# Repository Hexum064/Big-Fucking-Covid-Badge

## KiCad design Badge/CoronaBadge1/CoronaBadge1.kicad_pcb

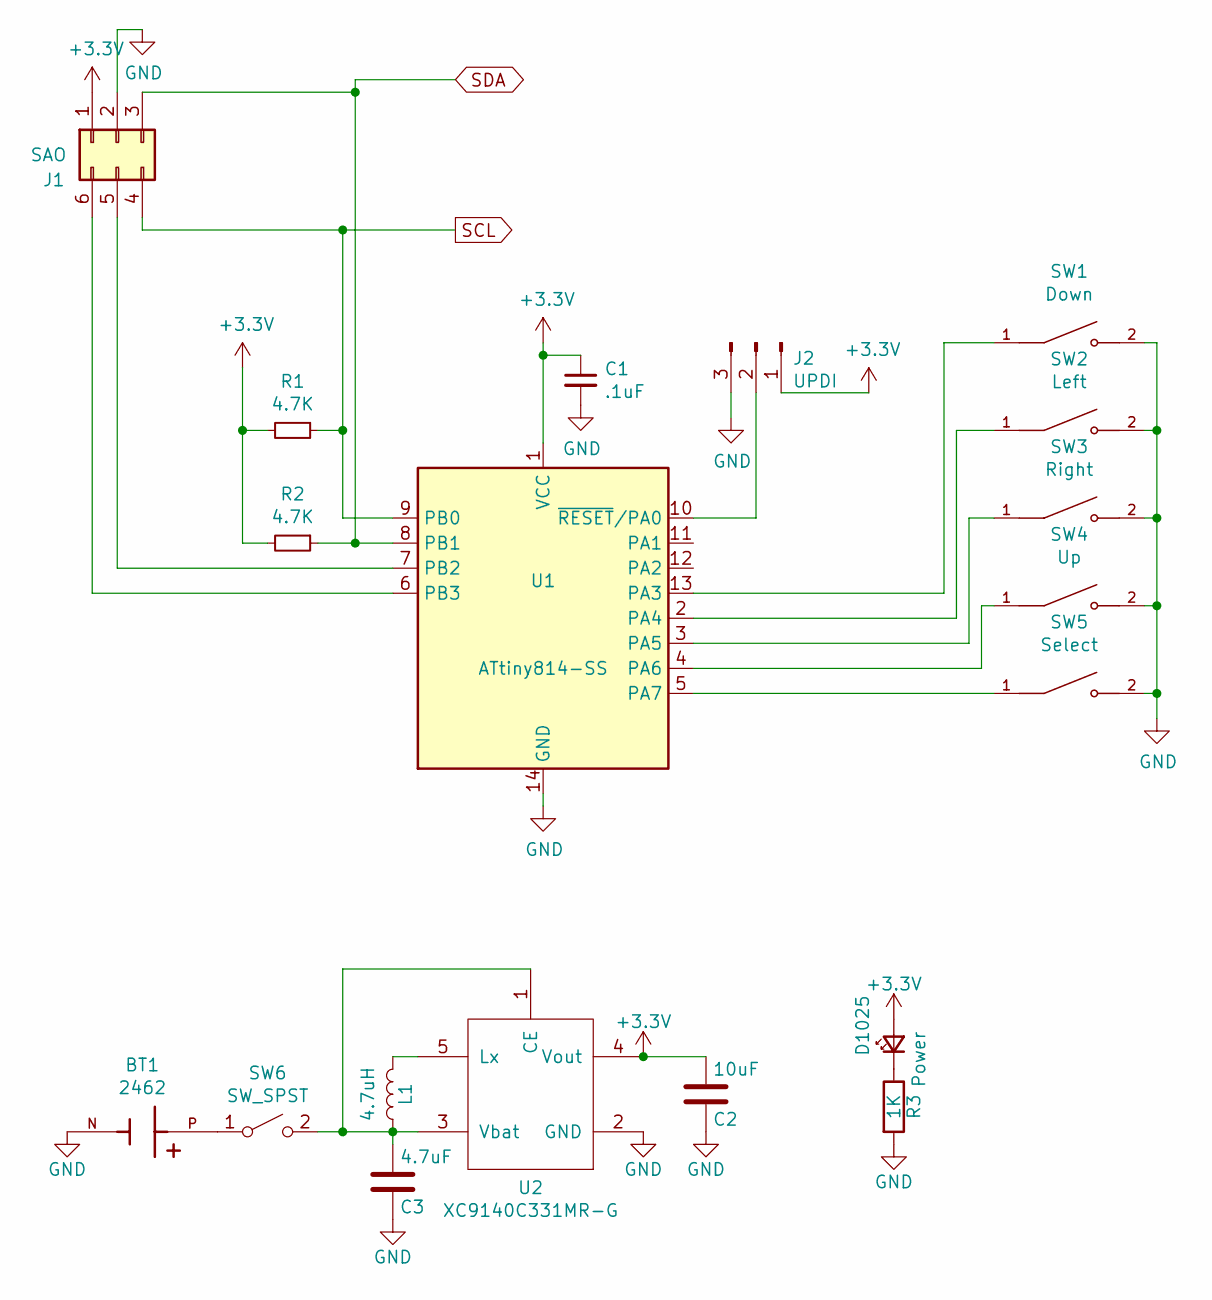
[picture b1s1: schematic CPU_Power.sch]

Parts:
BT1: 2462; BAT_2462; PARTREV G
C1: .1uF; C_0603
C2: 10uF; C_0603
C3: 4.7uF; C_0603
D1025: Power; LED_0603
J1: SAO; Pin_Header_Straight_2x03_Pitch2.54mm
J2: UPDI; Pin_Header_Straight_1x03_Pitch2.54mm
L1: 4.7uH; Inductor_Taiyo-Yuden_MD-3030
R1, R2: 4.7K; R_0603
R3: 1K; R_0603
SW1: Down; SW_PTS636_SM43J_SMTR_LFS
SW2: Left; SW_PTS636_SM43J_SMTR_LFS
SW3: Right; SW_PTS636_SM43J_SMTR_LFS
SW4: Up; SW_PTS636_SM43J_SMTR_LFS
SW5: Select; SW_PTS636_SM43J_SMTR_LFS
SW6: SW_SPST; MSS3VTR
U1: ATtiny814-SS; SOIC-14_3.9x8.7mm_P1.27mm
U2: XC9140C331MR-G; SOT-23-5

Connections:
+3V3: C1.1, C2.2, D1025.2 (A), J1.1, J2.1, R1.2, R2.2, U1.1 (VCC), U2.4 (Vout); also elsewhere on the board
GND: BT1.N, C1.2, C2.1, C3.1, J1.2, J2.3, R3.2, SW1.2, SW2.2, SW3.2, SW4.2, SW5.2, U1.14 (GND), U2.2 (GND); also elsewhere on the board
unnamed: BT1.P, SW6.1 (A)
unnamed: C3.2, L1.1, SW6.2 (B), U2.1 (CE), U2.3 (Vbat)
unnamed: D1025.1 (K), R3.1
unnamed: J1.5, U1.7 (PB2)
unnamed: J1.6, U1.6 (PB3)
unnamed: J2.2, U1.10 (~RESET~/PA0)
unnamed: L1.2, U2.5 (Lx)
unnamed: SW1.1, U1.13 (PA3)
unnamed: SW2.1, U1.2 (PA4)
unnamed: SW3.1, U1.3 (PA5)
unnamed: SW4.1, U1.4 (PA6)
unnamed: SW5.1, U1.5 (PA7)
SCL: J1.4, R1.1, U1.9 (PB0); also elsewhere on the board
SDA: J1.3, R2.1, U1.8 (PB1); also elsewhere on the board

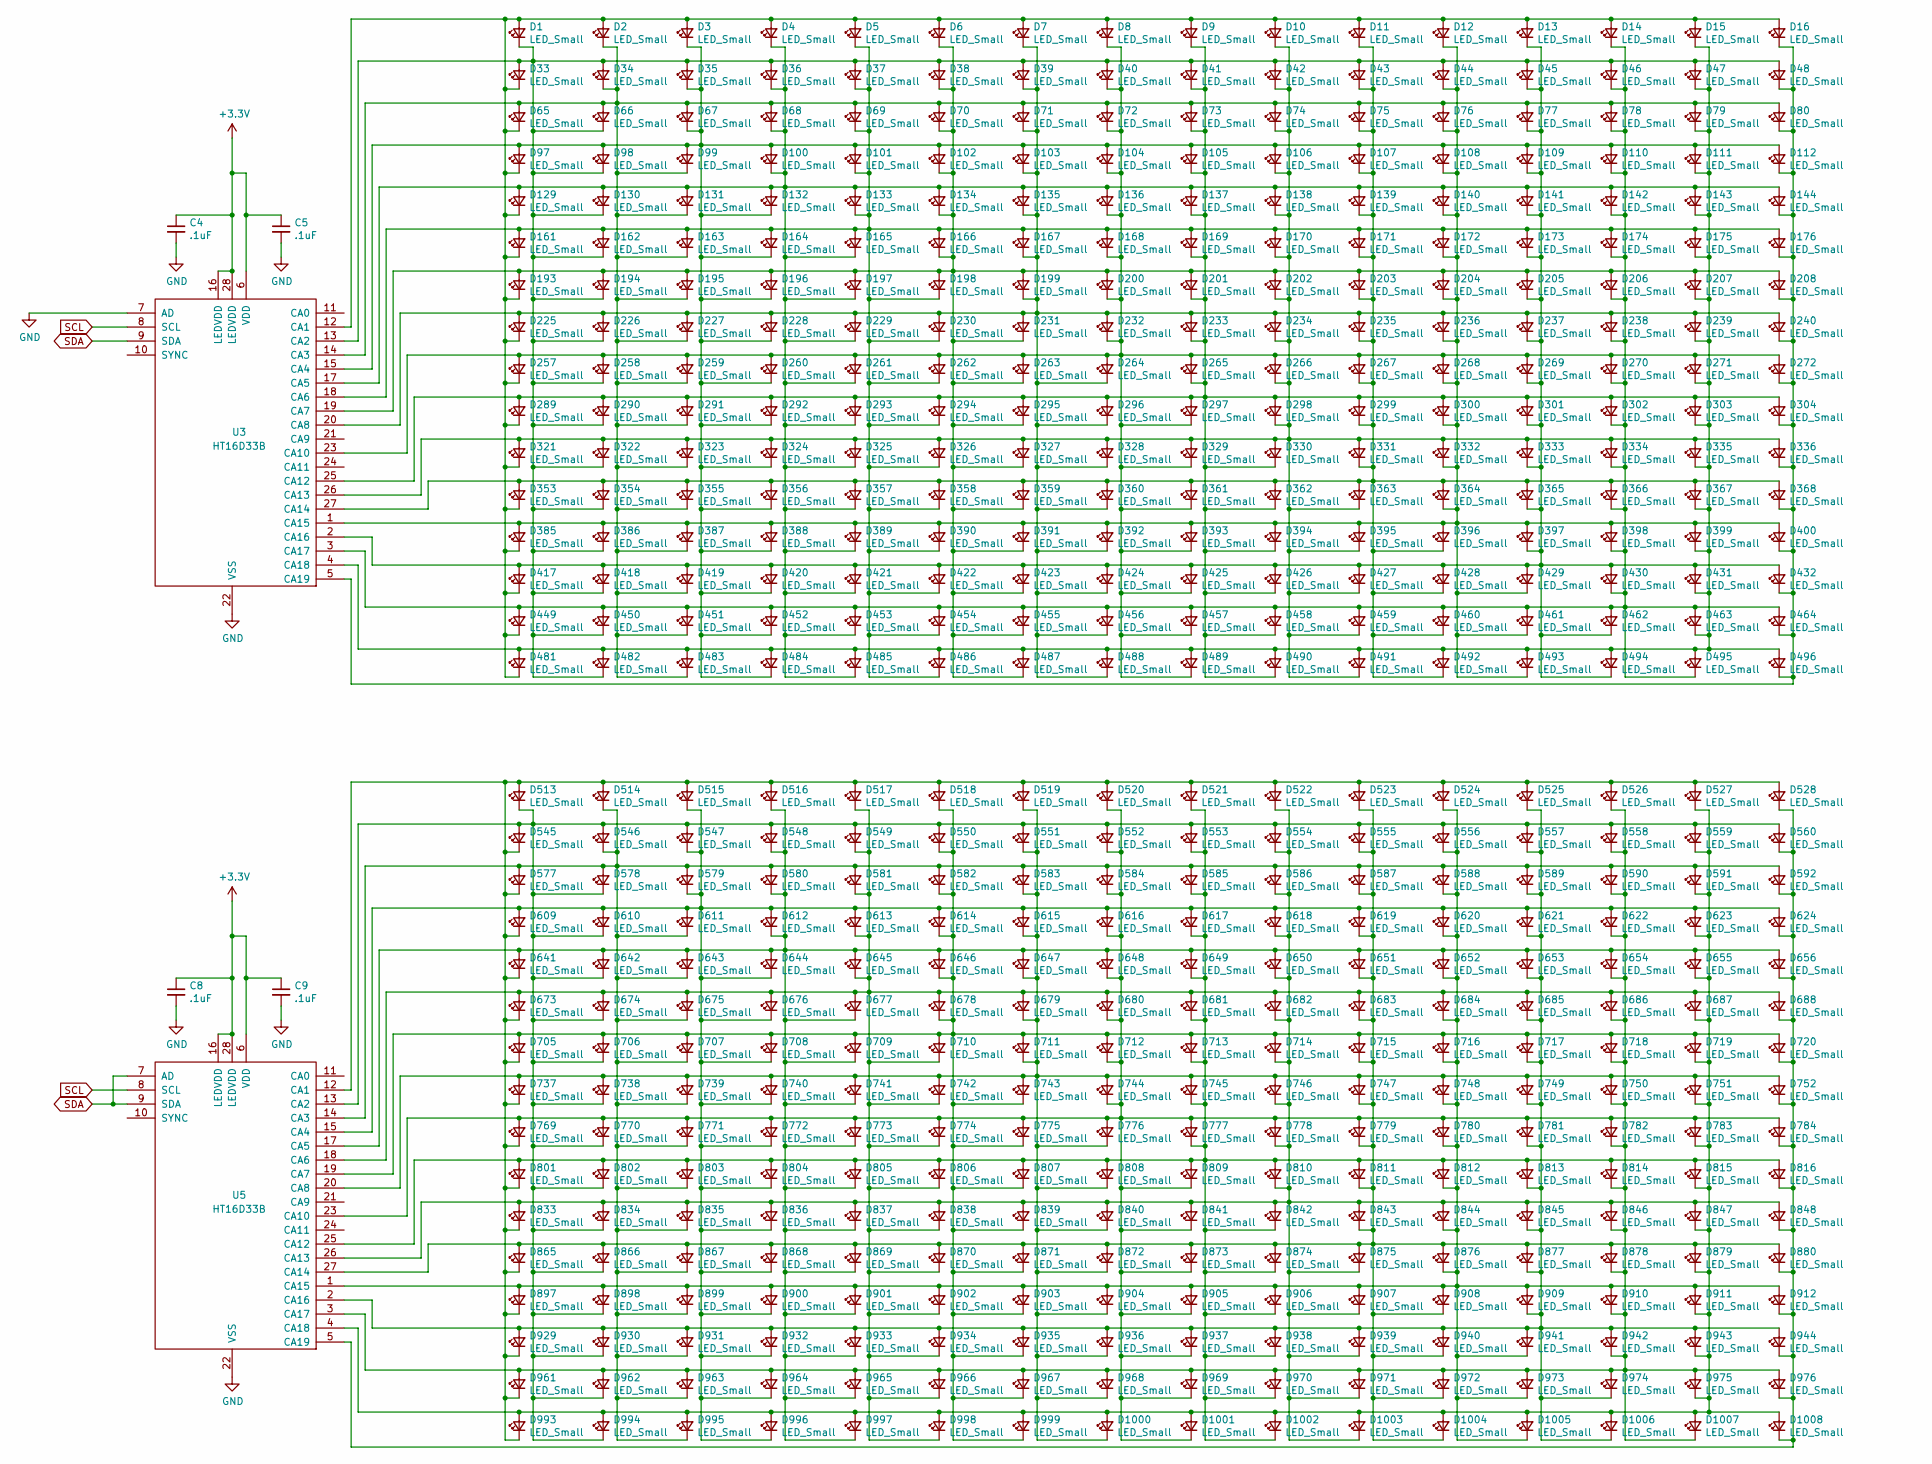
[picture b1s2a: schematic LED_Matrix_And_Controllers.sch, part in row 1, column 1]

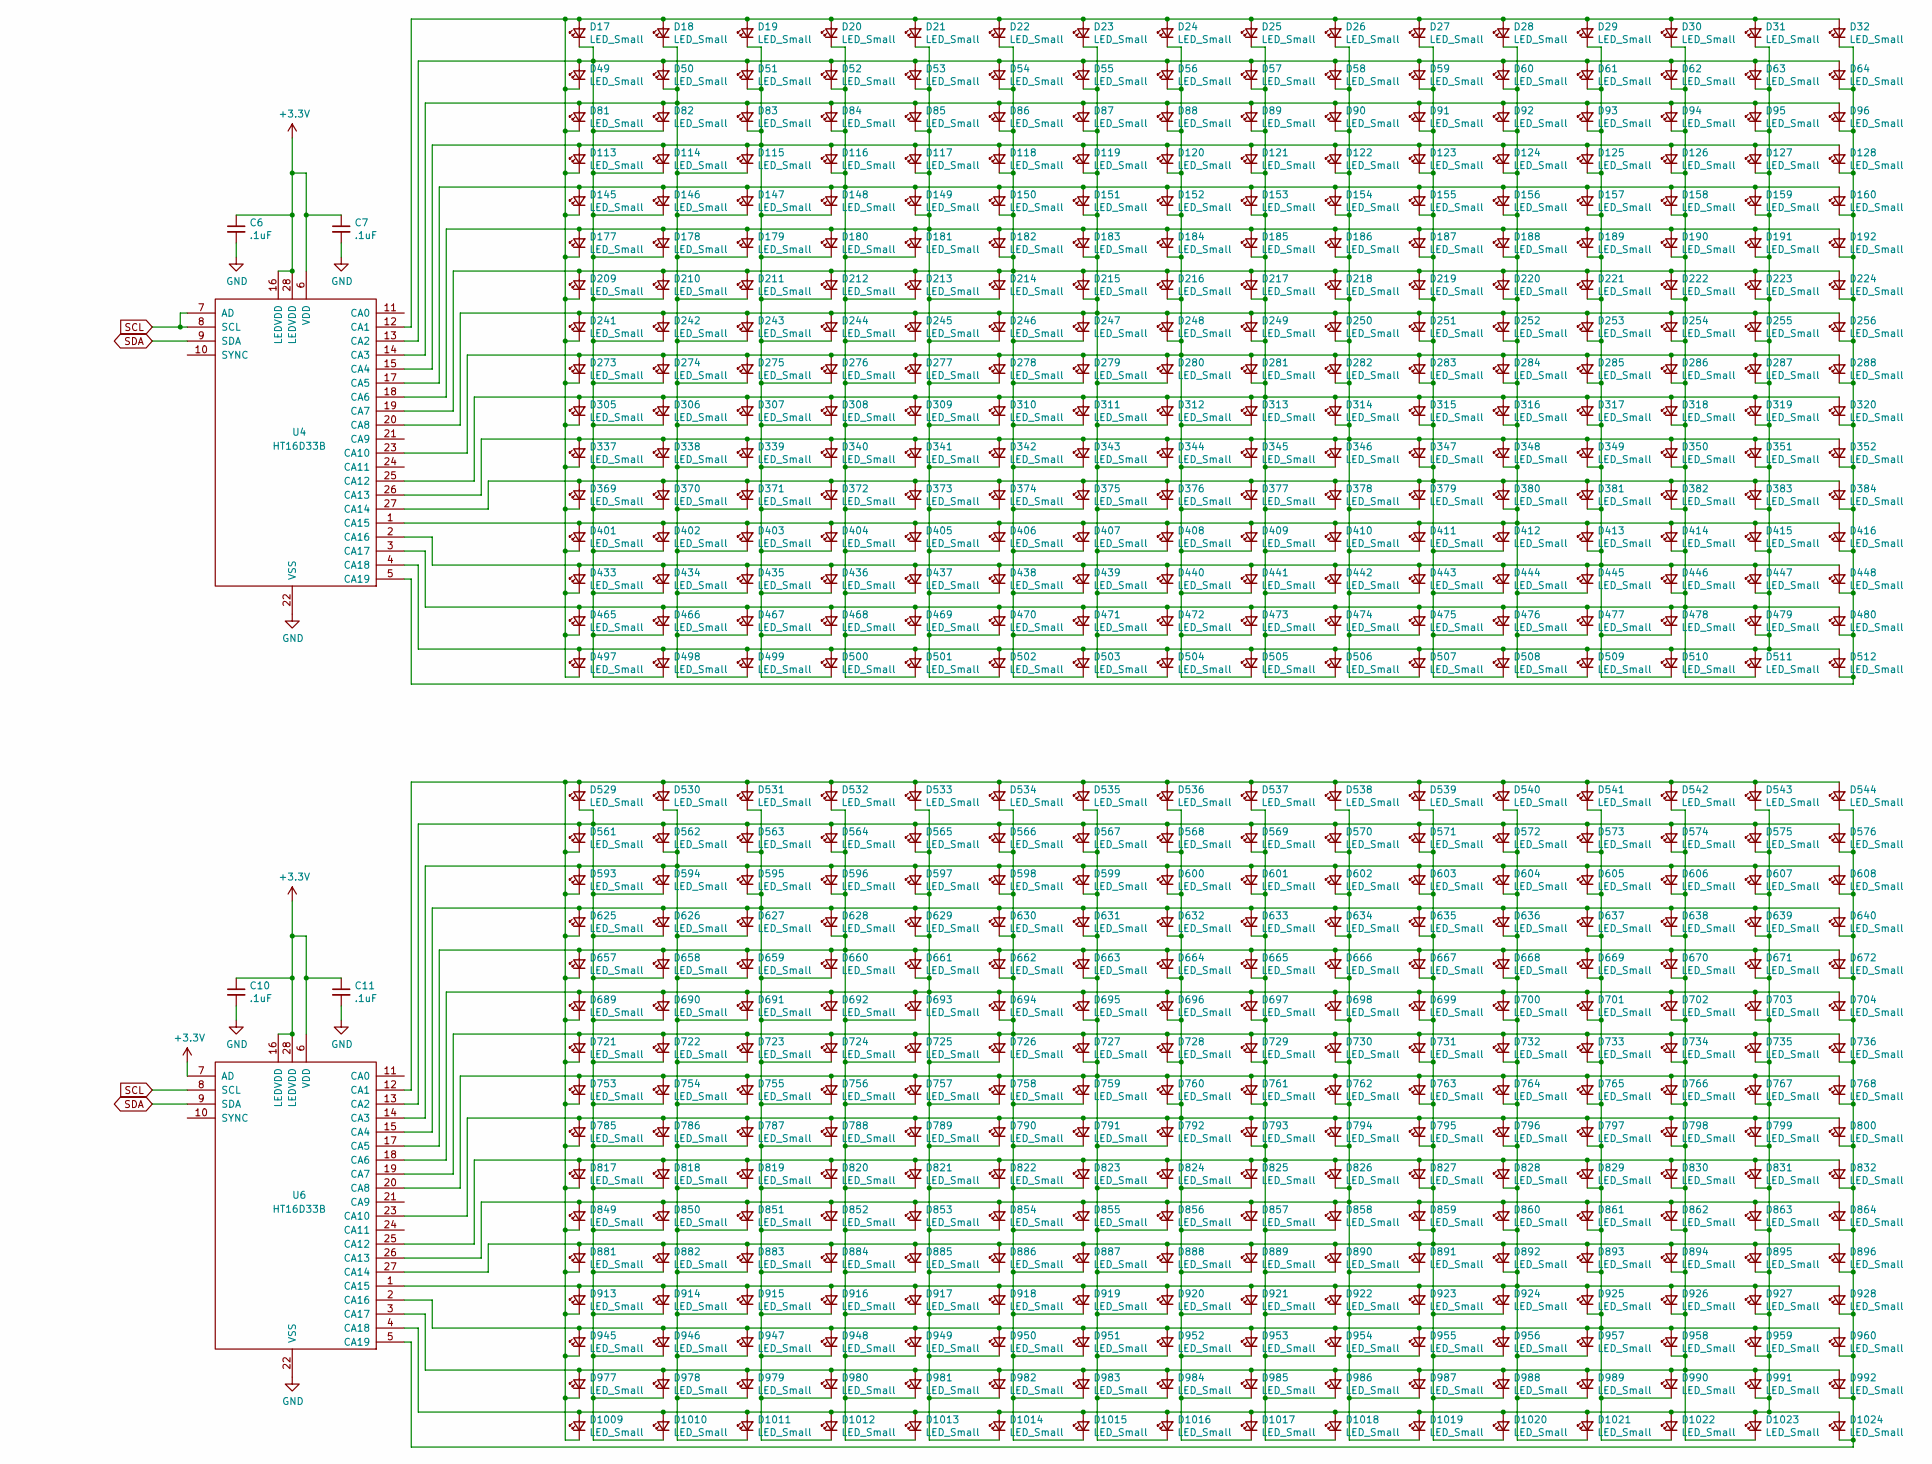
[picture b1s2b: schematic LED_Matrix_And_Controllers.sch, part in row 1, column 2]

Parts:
C4, C5, C6, C7, C8, C9, C10, C11: .1uF; C_0603
D1, D2, D3, D4, D5, D6, D7, D8, D9, D10, D11, D12, D13, D14, D15, D16, D17, D18, D19, D20, D21, D22, D23, D24, D25, D26, D27, D28, D29, D30, D31, D32, D33, D34, D35, D36, D37, D38, D39, D40, D41, D42, D43, D44, D45, D46, D47, D48, D49, D50, D51, D52, D53, D54, D55, D56, D57, D58, D59, D60, D61, D62, D63, D64, D65, D66, D67, D68, D69, D70, D71, D72, D73, D74, D75, D76, D77, D78, D79, D80, D81, D82, D83, D84, D85, D86, D87, D88, D89, D90, D91, D92, D93, D94, D95, D96, D97, D98, D99, D100, D101, D102, D103, D104, D105, D106, D107, D108, D109, D110, D111, D112, D113, D114, D115, D116, D117, D118, D119, D120, D121, D122, D123, D124, D125, D126, D127, D128, D129, D130, D131, D132, D133, D134, D135, D136, D137, D138, D139, D140, D141, D142, D143, D144, D145, D146, D147, D148, D149, D150, D151, D152, D153, D154, D155, D156, D157, D158, D159, D160, D161, D162, D163, D164, D165, D166, D167, D168, D169, D170, D171, D172, D173, D174, D175, D176, D177, D178, D179, D180, D181, D182, D183, D184, D185, D186, D187, D188, D189, D190, D191, D192, D193, D194, D195, D196, D197, D198, D199, D200, D201, D202, D203, D204, D205, D206, D207, D208, D209, D210, D211, D212, D213, D214, D215, D216, D217, D218, D219, D220, D221, D222, D223, D224, D225, D226, D227, D228, D229, D230, D231, D232, D233, D234, D235, D236, D237, D238, D239, D240, D241, D242, D243, D244, D245, D246, D247, D248, D249, D250, D251, D252, D253, D254, D255, D256, D257, D258, D259, D260, D261, D262, D263, D264, D265, D266, D267, D268, D269, D270, D271, D272, D273, D274, D275, D276, D277, D278, D279, D280, D281, D282, D283, D284, D285, D286, D287, D288, D289, D290, D291, D292, D293, D294, D295, D296, D297, D298, D299, D300, D301, D302, D303, D304, D305, D306, D307, D308, D309, D310, D311, D312, D313, D314, D315, D316, D317, D318, D319, D320, D321, D322, D323, D324, D325, D326, D327, D328, D329, D330, D331, D332, D333, D334, D335, D336, D337, D338, D339, D340, D341, D342, D343, D344, D345, D346, D347, D348, D349, D350, D351, D352, D353, D354, D355, D356, D357, D358, D359, D360, D361, D362, D363, D364, D365, D366, D367, D368, D369, D370, D371, D372, D373, D374, D375, D376, D377, D378, D379, D380, D381, D382, D383, D384, D385, D386, D387, D388, D389, D390, D391, D392, D393, D394, D395, D396, D397, D398, D399, D400, D401, D402, D403, D404, D405, D406, D407, D408, D409, D410, D411, D412, D413, D414, D415, D416, D417, D418, D419, D420, D421, D422, D423, D424, D425, D426, D427, D428, D429, D430, D431, D432, D433, D434, D435, D436, D437, D438, D439, D440, D441, D442, D443, D444, D445, D446, D447, D448, D449, D450, D451, D452, D453, D454, D455, D456, D457, D458, D459, D460, D461, D462, D463, D464, D465, D466, D467, D468, D469, D470, D471, D472, D473, D474, D475, D476, D477, D478, D479, D480, D481, D482, D483, D484, D485, D486, D487, D488, D489, D490, D491, D492, D493, D494, D495, D496, D497, D498, D499, D500, D501, D502, D503, D504, D505, D506, D507, D508, D509, D510, D511, D512, D513, D514, D515, D516, D517, D518, D519, D520, D521, D522, D523, D524, D525, D526, D527, D528, D529, D530, D531, D532, D533, D534, D535, D536, D537, D538, D539, D540, D541, D542, D543, D544, D545, D546, D547, D548, D549, D550, D551, D552, D553, D554, D555, D556, D557, D558, D559, D560, D561, D562, D563, D564, D565, D566, D567, D568, D569, D570, D571, D572, D573, D574, D575, D576, D577, D578, D579, D580, D581, D582, D583, D584, D585, D586, D587, D588, D589, D590, D591, D592, D593, D594, D595, D596, D597, D598, D599, D600, D601, D602, D603, D604, D605, D606, D607, D608, D609, D610, D611, D612, D613, D614, D615, D616, D617, D618, D619, D620, D621, D622, D623, D624, D625, D626, D627, D628, D629, D630, D631, D632, D633, D634, D635, D636, D637, D638, D639, D640, D641, D642, D643, D644, D645, D646, D647, D648, D649, D650, D651, D652, D653, D654, D655, D656, D657, D658, D659, D660, D661, D662, D663, D664, D665, D666, D667, D668, D669, D670, D671, D672, D673, D674, D675, D676, D677, D678, D679, D680, D681, D682, D683, D684, D685, D686, D687, D688, D689, D690, D691, D692, D693, D694, D695, D696, D697, D698, D699, D700, D701, D702, D703, D704, D705, D706, D707, D708, D709, D710, D711, D712, D713, D714, D715, D716, D717, D718, D719, D720, D721, D722, D723, D724, D725, D726, D727, D728, D729, D730, D731, D732, D733, D734, D735, D736, D737, D738, D739, D740, D741, D742, D743, D744, D745, D746, D747, D748, D749, D750, D751, D752, D753, D754, D755, D756, D757, D758, D759, D760, D761, D762, D763, D764, D765, D766, D767, D768, D769, D770, D771, D772, D773, D774, D775, D776, D777, D778, D779, D780, D781, D782, D783, D784, D785, D786, D787, D788, D789, D790, D791, D792, D793, D794, D795, D796, D797, D798, D799, D800, D801, D802, D803, D804, D805, D806, D807, D808, D809, D810, D811, D812, D813, D814, D815, D816, D817, D818, D819, D820, D821, D822, D823, D824, D825, D826, D827, D828, D829, D830, D831, D832, D833, D834, D835, D836, D837, D838, D839, D840, D841, D842, D843, D844, D845, D846, D847, D848, D849, D850, D851, D852, D853, D854, D855, D856, D857, D858, D859, D860, D861, D862, D863, D864, D865, D866, D867, D868, D869, D870, D871, D872, D873, D874, D875, D876, D877, D878, D879, D880, D881, D882, D883, D884, D885, D886, D887, D888, D889, D890, D891, D892, D893, D894, D895, D896, D897, D898, D899, D900, D901, D902, D903, D904, D905, D906, D907, D908, D909, D910, D911, D912, D913, D914, D915, D916, D917, D918, D919, D920, D921, D922, D923, D924, D925, D926, D927, D928, D929, D930, D931, D932, D933, D934, D935, D936, D937, D938, D939, D940, D941, D942, D943, D944, D945, D946, D947, D948, D949, D950, D951, D952, D953, D954, D955, D956, D957, D958, D959, D960, D961, D962, D963, D964, D965, D966, D967, D968, D969, D970, D971, D972, D973, D974, D975, D976, D977, D978, D979, D980, D981, D982, D983, D984, D985, D986, D987, D988, D989, D990, D991, D992, D993, D994, D995, D996, D997, D998, D999, D1000, D1001, D1002, D1003, D1004, D1005, D1006, D1007, D1008, D1009, D1010, D1011, D1012, D1013, D1014, D1015, D1016, D1017, D1018, D1019, D1020, D1021, D1022, D1023, D1024: LED_Small; LED_0603_No_SilkS_Ref
U3, U4, U5, U6: HT16D33B; SSOP-28_3.9x9.9mm_Pitch0.635mm

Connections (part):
+3V3: C4.1, C5.1, C6.1, C7.1, C8.1, C9.1, C10.1, C11.1, U3.6 (VDD), U3.16 (LEDVDD), U3.28 (LEDVDD), U4.6 (VDD), U4.16 (LEDVDD), U4.28 (LEDVDD), U5.6 (VDD), U5.16 (LEDVDD), U5.28 (LEDVDD), U6.6 (VDD), U6.7 (AD), U6.16 (LEDVDD), U6.28 (LEDVDD); also elsewhere on the board
GND: C4.2, C5.2, C6.2, C7.2, C8.2, C9.2, C10.2, C11.2, U3.7 (AD), U3.22 (VSS), U4.22 (VSS), U5.22 (VSS), U6.22 (VSS); also elsewhere on the board
unnamed: D1.1 (K), D33.2 (A), D34.2 (A), D35.2 (A), D36.2 (A), D37.2 (A), D38.2 (A), D39.2 (A), D40.2 (A), D41.2 (A), D42.2 (A), D43.2 (A), D44.2 (A), D45.2 (A), D46.2 (A), D47.2 (A), D48.2 (A), D66.1 (K), D98.1 (K), D130.1 (K), D162.1 (K), D194.1 (K), D226.1 (K), D258.1 (K), D290.1 (K), D322.1 (K), D354.1 (K), D386.1 (K), D418.1 (K), D450.1 (K), D482.1 (K), U3.13 (CA2)
unnamed: D1.2 (A), D2.2 (A), D3.2 (A), D4.2 (A), D5.2 (A), D6.2 (A), D7.2 (A), D8.2 (A), D9.2 (A), D10.2 (A), D11.2 (A), D12.2 (A), D13.2 (A), D14.2 (A), D15.2 (A), D16.2 (A), D33.1 (K), D65.1 (K), D97.1 (K), D129.1 (K), D161.1 (K), D193.1 (K), D225.1 (K), D257.1 (K), D289.1 (K), D321.1 (K), D353.1 (K), D385.1 (K), D417.1 (K), D449.1 (K), D481.1 (K), U3.12 (CA1)
unnamed: D10.1 (K), D42.1 (K), D74.1 (K), D106.1 (K), D138.1 (K), D170.1 (K), D202.1 (K), D234.1 (K), D266.1 (K), D298.1 (K), D321.2 (A), D322.2 (A), D323.2 (A), D324.2 (A), D325.2 (A), D326.2 (A), D327.2 (A), D328.2 (A), D329.2 (A), D330.2 (A), D331.2 (A), D332.2 (A), D333.2 (A), D334.2 (A), D335.2 (A), D336.2 (A), D363.1 (K), D395.1 (K), D427.1 (K), D459.1 (K), D491.1 (K), U3.26 (CA13)
unnamed: D4.1 (K), D36.1 (K), D68.1 (K), D100.1 (K), D129.2 (A), D130.2 (A), D131.2 (A), D132.2 (A), D133.2 (A), D134.2 (A), D135.2 (A), D136.2 (A), D137.2 (A), D138.2 (A), D139.2 (A), D140.2 (A), D141.2 (A), D142.2 (A), D143.2 (A), D144.2 (A), D165.1 (K), D197.1 (K), D229.1 (K), D261.1 (K), D293.1 (K), D325.1 (K), D357.1 (K), D389.1 (K), D421.1 (K), D453.1 (K), D485.1 (K), U3.17 (CA5)
unnamed: D3.1 (K), D35.1 (K), D67.1 (K), D97.2 (A), D98.2 (A), D99.2 (A), D100.2 (A), D101.2 (A), D102.2 (A), D103.2 (A), D104.2 (A), D105.2 (A), D106.2 (A), D107.2 (A), D108.2 (A), D109.2 (A), D110.2 (A), D111.2 (A), D112.2 (A), D132.1 (K), D164.1 (K), D196.1 (K), D228.1 (K), D260.1 (K), D292.1 (K), D324.1 (K), D356.1 (K), D388.1 (K), D420.1 (K), D452.1 (K), D484.1 (K), U3.15 (CA4)
unnamed: D5.1 (K), D37.1 (K), D69.1 (K), D101.1 (K), D133.1 (K), D161.2 (A), D162.2 (A), D163.2 (A), D164.2 (A), D165.2 (A), D166.2 (A), D167.2 (A), D168.2 (A), D169.2 (A), D170.2 (A), D171.2 (A), D172.2 (A), D173.2 (A), D174.2 (A), D175.2 (A), D176.2 (A), D198.1 (K), D230.1 (K), D262.1 (K), D294.1 (K), D326.1 (K), D358.1 (K), D390.1 (K), D422.1 (K), D454.1 (K), D486.1 (K), U3.18 (CA6)
unnamed: D6.1 (K), D38.1 (K), D70.1 (K), D102.1 (K), D134.1 (K), D166.1 (K), D193.2 (A), D194.2 (A), D195.2 (A), D196.2 (A), D197.2 (A), D198.2 (A), D199.2 (A), D200.2 (A), D201.2 (A), D202.2 (A), D203.2 (A), D204.2 (A), D205.2 (A), D206.2 (A), D207.2 (A), D208.2 (A), D231.1 (K), D263.1 (K), D295.1 (K), D327.1 (K), D359.1 (K), D391.1 (K), D423.1 (K), D455.1 (K), D487.1 (K), U3.19 (CA7)
unnamed: D7.1 (K), D39.1 (K), D71.1 (K), D103.1 (K), D135.1 (K), D167.1 (K), D199.1 (K), D225.2 (A), D226.2 (A), D227.2 (A), D228.2 (A), D229.2 (A), D230.2 (A), D231.2 (A), D232.2 (A), D233.2 (A), D234.2 (A), D235.2 (A), D236.2 (A), D237.2 (A), D238.2 (A), D239.2 (A), D240.2 (A), D264.1 (K), D296.1 (K), D328.1 (K), D360.1 (K), D392.1 (K), D424.1 (K), D456.1 (K), D488.1 (K), U3.20 (CA8)
unnamed: D8.1 (K), D40.1 (K), D72.1 (K), D104.1 (K), D136.1 (K), D168.1 (K), D200.1 (K), D232.1 (K), D257.2 (A), D258.2 (A), D259.2 (A), D260.2 (A), D261.2 (A), D262.2 (A), D263.2 (A), D264.2 (A), D265.2 (A), D266.2 (A), D267.2 (A), D268.2 (A), D269.2 (A), D270.2 (A), D271.2 (A), D272.2 (A), D297.1 (K), D329.1 (K), D361.1 (K), D393.1 (K), D425.1 (K), D457.1 (K), D489.1 (K), U3.23 (CA10)
unnamed: D9.1 (K), D41.1 (K), D73.1 (K), D105.1 (K), D137.1 (K), D169.1 (K), D201.1 (K), D233.1 (K), D265.1 (K), D289.2 (A), D290.2 (A), D291.2 (A), D292.2 (A), D293.2 (A), D294.2 (A), D295.2 (A), D296.2 (A), D297.2 (A), D298.2 (A), D299.2 (A), D300.2 (A), D301.2 (A), D302.2 (A), D303.2 (A), D304.2 (A), D330.1 (K), D362.1 (K), D394.1 (K), D426.1 (K), D458.1 (K), D490.1 (K), U3.25 (CA12)
unnamed: D11.1 (K), D43.1 (K), D75.1 (K), D107.1 (K), D139.1 (K), D171.1 (K), D203.1 (K), D235.1 (K), D267.1 (K), D299.1 (K), D331.1 (K), D353.2 (A), D354.2 (A), D355.2 (A), D356.2 (A), D357.2 (A), D358.2 (A), D359.2 (A), D360.2 (A), D361.2 (A), D362.2 (A), D363.2 (A), D364.2 (A), D365.2 (A), D366.2 (A), D367.2 (A), D368.2 (A), D396.1 (K), D428.1 (K), D460.1 (K), D492.1 (K), U3.27 (CA14)
unnamed: D12.1 (K), D44.1 (K), D76.1 (K), D108.1 (K), D140.1 (K), D172.1 (K), D204.1 (K), D236.1 (K), D268.1 (K), D300.1 (K), D332.1 (K), D364.1 (K), D385.2 (A), D386.2 (A), D387.2 (A), D388.2 (A), D389.2 (A), D390.2 (A), D391.2 (A), D392.2 (A), D393.2 (A), D394.2 (A), D395.2 (A), D396.2 (A), D397.2 (A), D398.2 (A), D399.2 (A), D400.2 (A), D429.1 (K), D461.1 (K), D493.1 (K), U3.1 (CA15)
unnamed: D13.1 (K), D45.1 (K), D77.1 (K), D109.1 (K), D141.1 (K), D173.1 (K), D205.1 (K), D237.1 (K), D269.1 (K), D301.1 (K), D333.1 (K), D365.1 (K), D397.1 (K), D417.2 (A), D418.2 (A), D419.2 (A), D420.2 (A), D421.2 (A), D422.2 (A), D423.2 (A), D424.2 (A), D425.2 (A), D426.2 (A), D427.2 (A), D428.2 (A), D429.2 (A), D430.2 (A), D431.2 (A), D432.2 (A), D462.1 (K), D494.1 (K), U3.2 (CA16)
unnamed: D14.1 (K), D46.1 (K), D78.1 (K), D110.1 (K), D142.1 (K), D174.1 (K), D206.1 (K), D238.1 (K), D270.1 (K), D302.1 (K), D334.1 (K), D366.1 (K), D398.1 (K), D430.1 (K), D449.2 (A), D450.2 (A), D451.2 (A), D452.2 (A), D453.2 (A), D454.2 (A), D455.2 (A), D456.2 (A), D457.2 (A), D458.2 (A), D459.2 (A), D460.2 (A), D461.2 (A), D462.2 (A), D463.2 (A), D464.2 (A), D495.1 (K), U3.3 (CA17)
unnamed: D15.1 (K), D47.1 (K), D79.1 (K), D111.1 (K), D143.1 (K), D175.1 (K), D207.1 (K), D239.1 (K), D271.1 (K), D303.1 (K), D335.1 (K), D367.1 (K), D399.1 (K), D431.1 (K), D463.1 (K), D481.2 (A), D482.2 (A), D483.2 (A), D484.2 (A), D485.2 (A), D486.2 (A), D487.2 (A), D488.2 (A), D489.2 (A), D490.2 (A), D491.2 (A), D492.2 (A), D493.2 (A), D494.2 (A), D495.2 (A), D496.2 (A), U3.4 (CA18)
unnamed: D16.1 (K), D48.1 (K), D80.1 (K), D112.1 (K), D144.1 (K), D176.1 (K), D208.1 (K), D240.1 (K), D272.1 (K), D304.1 (K), D336.1 (K), D368.1 (K), D400.1 (K), D432.1 (K), D464.1 (K), D496.1 (K), U3.5 (CA19)
unnamed: D17.2 (A), D18.2 (A), D19.2 (A), D20.2 (A), D21.2 (A), D22.2 (A), D23.2 (A), D24.2 (A), D25.2 (A), D26.2 (A), D27.2 (A), D28.2 (A), D29.2 (A), D30.2 (A), D31.2 (A), D32.2 (A), D49.1 (K), D81.1 (K), D113.1 (K), D145.1 (K), D177.1 (K), D209.1 (K), D241.1 (K), D273.1 (K), D305.1 (K), D337.1 (K), D369.1 (K), D401.1 (K), D433.1 (K), D465.1 (K), D497.1 (K), U4.12 (CA1)
unnamed: D19.1 (K), D51.1 (K), D83.1 (K), D113.2 (A), D114.2 (A), D115.2 (A), D116.2 (A), D117.2 (A), D118.2 (A), D119.2 (A), D120.2 (A), D121.2 (A), D122.2 (A), D123.2 (A), D124.2 (A), D125.2 (A), D126.2 (A), D127.2 (A), D128.2 (A), D148.1 (K), D180.1 (K), D212.1 (K), D244.1 (K), D276.1 (K), D308.1 (K), D340.1 (K), D372.1 (K), D404.1 (K), D436.1 (K), D468.1 (K), D500.1 (K), U4.15 (CA4)
unnamed: D17.1 (K), D49.2 (A), D50.2 (A), D51.2 (A), D52.2 (A), D53.2 (A), D54.2 (A), D55.2 (A), D56.2 (A), D57.2 (A), D58.2 (A), D59.2 (A), D60.2 (A), D61.2 (A), D62.2 (A), D63.2 (A), D64.2 (A), D82.1 (K), D114.1 (K), D146.1 (K), D178.1 (K), D210.1 (K), D242.1 (K), D274.1 (K), D306.1 (K), D338.1 (K), D370.1 (K), D402.1 (K), D434.1 (K), D466.1 (K), D498.1 (K), U4.13 (CA2)
unnamed: D18.1 (K), D50.1 (K), D81.2 (A), D82.2 (A), D83.2 (A), D84.2 (A), D85.2 (A), D86.2 (A), D87.2 (A), D88.2 (A), D89.2 (A), D90.2 (A), D91.2 (A), D92.2 (A), D93.2 (A), D94.2 (A), D95.2 (A), D96.2 (A), D115.1 (K), D147.1 (K), D179.1 (K), D211.1 (K), D243.1 (K), D275.1 (K), D307.1 (K), D339.1 (K), D371.1 (K), D403.1 (K), D435.1 (K), D467.1 (K), D499.1 (K), U4.14 (CA3)
unnamed: D20.1 (K), D52.1 (K), D84.1 (K), D116.1 (K), D145.2 (A), D146.2 (A), D147.2 (A), D148.2 (A), D149.2 (A), D150.2 (A), D151.2 (A), D152.2 (A), D153.2 (A), D154.2 (A), D155.2 (A), D156.2 (A), D157.2 (A), D158.2 (A), D159.2 (A), D160.2 (A), D181.1 (K), D213.1 (K), D245.1 (K), D277.1 (K), D309.1 (K), D341.1 (K), D373.1 (K), D405.1 (K), D437.1 (K), D469.1 (K), D501.1 (K), U4.17 (CA5)
unnamed: D21.1 (K), D53.1 (K), D85.1 (K), D117.1 (K), D149.1 (K), D177.2 (A), D178.2 (A), D179.2 (A), D180.2 (A), D181.2 (A), D182.2 (A), D183.2 (A), D184.2 (A), D185.2 (A), D186.2 (A), D187.2 (A), D188.2 (A), D189.2 (A), D190.2 (A), D191.2 (A), D192.2 (A), D214.1 (K), D246.1 (K), D278.1 (K), D310.1 (K), D342.1 (K), D374.1 (K), D406.1 (K), D438.1 (K), D470.1 (K), D502.1 (K), U4.18 (CA6)
unnamed: D22.1 (K), D54.1 (K), D86.1 (K), D118.1 (K), D150.1 (K), D182.1 (K), D209.2 (A), D210.2 (A), D211.2 (A), D212.2 (A), D213.2 (A), D214.2 (A), D215.2 (A), D216.2 (A), D217.2 (A), D218.2 (A), D219.2 (A), D220.2 (A), D221.2 (A), D222.2 (A), D223.2 (A), D224.2 (A), D247.1 (K), D279.1 (K), D311.1 (K), D343.1 (K), D375.1 (K), D407.1 (K), D439.1 (K), D471.1 (K), D503.1 (K), U4.19 (CA7)
unnamed: D23.1 (K), D55.1 (K), D87.1 (K), D119.1 (K), D151.1 (K), D183.1 (K), D215.1 (K), D241.2 (A), D242.2 (A), D243.2 (A), D244.2 (A), D245.2 (A), D246.2 (A), D247.2 (A), D248.2 (A), D249.2 (A), D250.2 (A), D251.2 (A), D252.2 (A), D253.2 (A), D254.2 (A), D255.2 (A), D256.2 (A), D280.1 (K), D312.1 (K), D344.1 (K), D376.1 (K), D408.1 (K), D440.1 (K), D472.1 (K), D504.1 (K), U4.20 (CA8)
unnamed: D24.1 (K), D56.1 (K), D88.1 (K), D120.1 (K), D152.1 (K), D184.1 (K), D216.1 (K), D248.1 (K), D273.2 (A), D274.2 (A), D275.2 (A), D276.2 (A), D277.2 (A), D278.2 (A), D279.2 (A), D280.2 (A), D281.2 (A), D282.2 (A), D283.2 (A), D284.2 (A), D285.2 (A), D286.2 (A), D287.2 (A), D288.2 (A), D313.1 (K), D345.1 (K), D377.1 (K), D409.1 (K), D441.1 (K), D473.1 (K), D505.1 (K), U4.23 (CA10)
unnamed: D25.1 (K), D57.1 (K), D89.1 (K), D121.1 (K), D153.1 (K), D185.1 (K), D217.1 (K), D249.1 (K), D281.1 (K), D305.2 (A), D306.2 (A), D307.2 (A), D308.2 (A), D309.2 (A), D310.2 (A), D311.2 (A), D312.2 (A), D313.2 (A), D314.2 (A), D315.2 (A), D316.2 (A), D317.2 (A), D318.2 (A), D319.2 (A), D320.2 (A), D346.1 (K), D378.1 (K), D410.1 (K), D442.1 (K), D474.1 (K), D506.1 (K), U4.25 (CA12)
unnamed: D26.1 (K), D58.1 (K), D90.1 (K), D122.1 (K), D154.1 (K), D186.1 (K), D218.1 (K), D250.1 (K), D282.1 (K), D314.1 (K), D337.2 (A), D338.2 (A), D339.2 (A), D340.2 (A), D341.2 (A), D342.2 (A), D343.2 (A), D344.2 (A), D345.2 (A), D346.2 (A), D347.2 (A), D348.2 (A), D349.2 (A), D350.2 (A), D351.2 (A), D352.2 (A), D379.1 (K), D411.1 (K), D443.1 (K), D475.1 (K), D507.1 (K), U4.26 (CA13)
unnamed: D27.1 (K), D59.1 (K), D91.1 (K), D123.1 (K), D155.1 (K), D187.1 (K), D219.1 (K), D251.1 (K), D283.1 (K), D315.1 (K), D347.1 (K), D369.2 (A), D370.2 (A), D371.2 (A), D372.2 (A), D373.2 (A), D374.2 (A), D375.2 (A), D376.2 (A), D377.2 (A), D378.2 (A), D379.2 (A), D380.2 (A), D381.2 (A), D382.2 (A), D383.2 (A), D384.2 (A), D412.1 (K), D444.1 (K), D476.1 (K), D508.1 (K), U4.27 (CA14)
unnamed: D28.1 (K), D60.1 (K), D92.1 (K), D124.1 (K), D156.1 (K), D188.1 (K), D220.1 (K), D252.1 (K), D284.1 (K), D316.1 (K), D348.1 (K), D380.1 (K), D401.2 (A), D402.2 (A), D403.2 (A), D404.2 (A), D405.2 (A), D406.2 (A), D407.2 (A), D408.2 (A), D409.2 (A), D410.2 (A), D411.2 (A), D412.2 (A), D413.2 (A), D414.2 (A), D415.2 (A), D416.2 (A), D445.1 (K), D477.1 (K), D509.1 (K), U4.1 (CA15)
unnamed: D29.1 (K), D61.1 (K), D93.1 (K), D125.1 (K), D157.1 (K), D189.1 (K), D221.1 (K), D253.1 (K), D285.1 (K), D317.1 (K), D349.1 (K), D381.1 (K), D413.1 (K), D433.2 (A), D434.2 (A), D435.2 (A), D436.2 (A), D437.2 (A), D438.2 (A), D439.2 (A), D440.2 (A), D441.2 (A), D442.2 (A), D443.2 (A), D444.2 (A), D445.2 (A), D446.2 (A), D447.2 (A), D448.2 (A), D478.1 (K), D510.1 (K), U4.2 (CA16)
unnamed: D30.1 (K), D62.1 (K), D94.1 (K), D126.1 (K), D158.1 (K), D190.1 (K), D222.1 (K), D254.1 (K), D286.1 (K), D318.1 (K), D350.1 (K), D382.1 (K), D414.1 (K), D446.1 (K), D465.2 (A), D466.2 (A), D467.2 (A), D468.2 (A), D469.2 (A), D470.2 (A), D471.2 (A), D472.2 (A), D473.2 (A), D474.2 (A), D475.2 (A), D476.2 (A), D477.2 (A), D478.2 (A), D479.2 (A), D480.2 (A), D511.1 (K), U4.3 (CA17)
unnamed: D31.1 (K), D63.1 (K), D95.1 (K), D127.1 (K), D159.1 (K), D191.1 (K), D223.1 (K), D255.1 (K), D287.1 (K), D319.1 (K), D351.1 (K), D383.1 (K), D415.1 (K), D447.1 (K), D479.1 (K), D497.2 (A), D498.2 (A), D499.2 (A), D500.2 (A), D501.2 (A), D502.2 (A), D503.2 (A), D504.2 (A), D505.2 (A), D506.2 (A), D507.2 (A), D508.2 (A), D509.2 (A), D510.2 (A), D511.2 (A), D512.2 (A), U4.4 (CA18)
unnamed: D32.1 (K), D64.1 (K), D96.1 (K), D128.1 (K), D160.1 (K), D192.1 (K), D224.1 (K), D256.1 (K), D288.1 (K), D320.1 (K), D352.1 (K), D384.1 (K), D416.1 (K), D448.1 (K), D480.1 (K), D512.1 (K), U4.5 (CA19)
unnamed: D2.1 (K), D34.1 (K), D65.2 (A), D66.2 (A), D67.2 (A), D68.2 (A), D69.2 (A), D70.2 (A), D71.2 (A), D72.2 (A), D73.2 (A), D74.2 (A), D75.2 (A), D76.2 (A), D77.2 (A), D78.2 (A), D79.2 (A), D80.2 (A), D99.1 (K), D131.1 (K), D163.1 (K), D195.1 (K), D227.1 (K), D259.1 (K), D291.1 (K), D323.1 (K), D355.1 (K), D387.1 (K), D419.1 (K), D451.1 (K), D483.1 (K), U3.14 (CA3)
unnamed: D513.1 (K), D545.2 (A), D546.2 (A), D547.2 (A), D548.2 (A), D549.2 (A), D550.2 (A), D551.2 (A), D552.2 (A), D553.2 (A), D554.2 (A), D555.2 (A), D556.2 (A), D557.2 (A), D558.2 (A), D559.2 (A), D560.2 (A), D578.1 (K), D610.1 (K), D642.1 (K), D674.1 (K), D706.1 (K), D738.1 (K), D770.1 (K), D802.1 (K), D834.1 (K), D866.1 (K), D898.1 (K), D930.1 (K), D962.1 (K), D994.1 (K), U5.13 (CA2)
unnamed: D513.2 (A), D514.2 (A), D515.2 (A), D516.2 (A), D517.2 (A), D518.2 (A), D519.2 (A), D520.2 (A), D521.2 (A), D522.2 (A), D523.2 (A), D524.2 (A), D525.2 (A), D526.2 (A), D527.2 (A), D528.2 (A), D545.1 (K), D577.1 (K), D609.1 (K), D641.1 (K), D673.1 (K), D705.1 (K), D737.1 (K), D769.1 (K), D801.1 (K), D833.1 (K), D865.1 (K), D897.1 (K), D929.1 (K), D961.1 (K), D993.1 (K), U5.12 (CA1)
unnamed: D514.1 (K), D546.1 (K), D577.2 (A), D578.2 (A), D579.2 (A), D580.2 (A), D581.2 (A), D582.2 (A), D583.2 (A), D584.2 (A), D585.2 (A), D586.2 (A), D587.2 (A), D588.2 (A), D589.2 (A), D590.2 (A), D591.2 (A), D592.2 (A), D611.1 (K), D643.1 (K), D675.1 (K), D707.1 (K), D739.1 (K), D771.1 (K), D803.1 (K), D835.1 (K), D867.1 (K), D899.1 (K), D931.1 (K), D963.1 (K), D995.1 (K), U5.14 (CA3)
unnamed: D515.1 (K), D547.1 (K), D579.1 (K), D609.2 (A), D610.2 (A), D611.2 (A), D612.2 (A), D613.2 (A), D614.2 (A), D615.2 (A), D616.2 (A), D617.2 (A), D618.2 (A), D619.2 (A), D620.2 (A), D621.2 (A), D622.2 (A), D623.2 (A), D624.2 (A), D644.1 (K), D676.1 (K), D708.1 (K), D740.1 (K), D772.1 (K), D804.1 (K), D836.1 (K), D868.1 (K), D900.1 (K), D932.1 (K), D964.1 (K), D996.1 (K), U5.15 (CA4)
unnamed: D516.1 (K), D548.1 (K), D580.1 (K), D612.1 (K), D641.2 (A), D642.2 (A), D643.2 (A), D644.2 (A), D645.2 (A), D646.2 (A), D647.2 (A), D648.2 (A), D649.2 (A), D650.2 (A), D651.2 (A), D652.2 (A), D653.2 (A), D654.2 (A), D655.2 (A), D656.2 (A), D677.1 (K), D709.1 (K), D741.1 (K), D773.1 (K), D805.1 (K), D837.1 (K), D869.1 (K), D901.1 (K), D933.1 (K), D965.1 (K), D997.1 (K), U5.17 (CA5)
unnamed: D517.1 (K), D549.1 (K), D581.1 (K), D613.1 (K), D645.1 (K), D673.2 (A), D674.2 (A), D675.2 (A), D676.2 (A), D677.2 (A), D678.2 (A), D679.2 (A), D680.2 (A), D681.2 (A), D682.2 (A), D683.2 (A), D684.2 (A), D685.2 (A), D686.2 (A), D687.2 (A), D688.2 (A), D710.1 (K), D742.1 (K), D774.1 (K), D806.1 (K), D838.1 (K), D870.1 (K), D902.1 (K), D934.1 (K), D966.1 (K), D998.1 (K), U5.18 (CA6)
unnamed: D518.1 (K), D550.1 (K), D582.1 (K), D614.1 (K), D646.1 (K), D678.1 (K), D705.2 (A), D706.2 (A), D707.2 (A), D708.2 (A), D709.2 (A), D710.2 (A), D711.2 (A), D712.2 (A), D713.2 (A), D714.2 (A), D715.2 (A), D716.2 (A), D717.2 (A), D718.2 (A), D719.2 (A), D720.2 (A), D743.1 (K), D775.1 (K), D807.1 (K), D839.1 (K), D871.1 (K), D903.1 (K), D935.1 (K), D967.1 (K), D999.1 (K), U5.19 (CA7)
unnamed: D519.1 (K), D551.1 (K), D583.1 (K), D615.1 (K), D647.1 (K), D679.1 (K), D711.1 (K), D737.2 (A), D738.2 (A), D739.2 (A), D740.2 (A), D741.2 (A), D742.2 (A), D743.2 (A), D744.2 (A), D745.2 (A), D746.2 (A), D747.2 (A), D748.2 (A), D749.2 (A), D750.2 (A), D751.2 (A), D752.2 (A), D776.1 (K), D808.1 (K), D840.1 (K), D872.1 (K), D904.1 (K), D936.1 (K), D968.1 (K), D1000.1 (K), U5.20 (CA8)
unnamed: D527.1 (K), D559.1 (K), D591.1 (K), D623.1 (K), D655.1 (K), D687.1 (K), D719.1 (K), D751.1 (K), D783.1 (K), D815.1 (K), D847.1 (K), D879.1 (K), D911.1 (K), D943.1 (K), D975.1 (K), D993.2 (A), D994.2 (A), D995.2 (A), D996.2 (A), D997.2 (A), D998.2 (A), D999.2 (A), D1000.2 (A), D1001.2 (A), D1002.2 (A), D1003.2 (A), D1004.2 (A), D1005.2 (A), D1006.2 (A), D1007.2 (A), D1008.2 (A), U5.4 (CA18)
unnamed: D520.1 (K), D552.1 (K), D584.1 (K), D616.1 (K), D648.1 (K), D680.1 (K), D712.1 (K), D744.1 (K), D769.2 (A), D770.2 (A), D771.2 (A), D772.2 (A), D773.2 (A), D774.2 (A), D775.2 (A), D776.2 (A), D777.2 (A), D778.2 (A), D779.2 (A), D780.2 (A), D781.2 (A), D782.2 (A), D783.2 (A), D784.2 (A), D809.1 (K), D841.1 (K), D873.1 (K), D905.1 (K), D937.1 (K), D969.1 (K), D1001.1 (K), U5.23 (CA10)
unnamed: D521.1 (K), D553.1 (K), D585.1 (K), D617.1 (K), D649.1 (K), D681.1 (K), D713.1 (K), D745.1 (K), D777.1 (K), D801.2 (A), D802.2 (A), D803.2 (A), D804.2 (A), D805.2 (A), D806.2 (A), D807.2 (A), D808.2 (A), D809.2 (A), D810.2 (A), D811.2 (A), D812.2 (A), D813.2 (A), D814.2 (A), D815.2 (A), D816.2 (A), D842.1 (K), D874.1 (K), D906.1 (K), D938.1 (K), D970.1 (K), D1002.1 (K), U5.25 (CA12)
unnamed: D522.1 (K), D554.1 (K), D586.1 (K), D618.1 (K), D650.1 (K), D682.1 (K), D714.1 (K), D746.1 (K), D778.1 (K), D810.1 (K), D833.2 (A), D834.2 (A), D835.2 (A), D836.2 (A), D837.2 (A), D838.2 (A), D839.2 (A), D840.2 (A), D841.2 (A), D842.2 (A), D843.2 (A), D844.2 (A), D845.2 (A), D846.2 (A), D847.2 (A), D848.2 (A), D875.1 (K), D907.1 (K), D939.1 (K), D971.1 (K), D1003.1 (K), U5.26 (CA13)
unnamed: D523.1 (K), D555.1 (K), D587.1 (K), D619.1 (K), D651.1 (K), D683.1 (K), D715.1 (K), D747.1 (K), D779.1 (K), D811.1 (K), D843.1 (K), D865.2 (A), D866.2 (A), D867.2 (A), D868.2 (A), D869.2 (A), D870.2 (A), D871.2 (A), D872.2 (A), D873.2 (A), D874.2 (A), D875.2 (A), D876.2 (A), D877.2 (A), D878.2 (A), D879.2 (A), D880.2 (A), D908.1 (K), D940.1 (K), D972.1 (K), D1004.1 (K), U5.27 (CA14)
unnamed: D524.1 (K), D556.1 (K), D588.1 (K), D620.1 (K), D652.1 (K), D684.1 (K), D716.1 (K), D748.1 (K), D780.1 (K), D812.1 (K), D844.1 (K), D876.1 (K), D897.2 (A), D898.2 (A), D899.2 (A), D900.2 (A), D901.2 (A), D902.2 (A), D903.2 (A), D904.2 (A), D905.2 (A), D906.2 (A), D907.2 (A), D908.2 (A), D909.2 (A), D910.2 (A), D911.2 (A), D912.2 (A), D941.1 (K), D973.1 (K), D1005.1 (K), U5.1 (CA15)
unnamed: D525.1 (K), D557.1 (K), D589.1 (K), D621.1 (K), D653.1 (K), D685.1 (K), D717.1 (K), D749.1 (K), D781.1 (K), D813.1 (K), D845.1 (K), D877.1 (K), D909.1 (K), D929.2 (A), D930.2 (A), D931.2 (A), D932.2 (A), D933.2 (A), D934.2 (A), D935.2 (A), D936.2 (A), D937.2 (A), D938.2 (A), D939.2 (A), D940.2 (A), D941.2 (A), D942.2 (A), D943.2 (A), D944.2 (A), D974.1 (K), D1006.1 (K), U5.2 (CA16)
unnamed: D526.1 (K), D558.1 (K), D590.1 (K), D622.1 (K), D654.1 (K), D686.1 (K), D718.1 (K), D750.1 (K), D782.1 (K), D814.1 (K), D846.1 (K), D878.1 (K), D910.1 (K), D942.1 (K), D961.2 (A), D962.2 (A), D963.2 (A), D964.2 (A), D965.2 (A), D966.2 (A), D967.2 (A), D968.2 (A), D969.2 (A), D970.2 (A), D971.2 (A), D972.2 (A), D973.2 (A), D974.2 (A), D975.2 (A), D976.2 (A), D1007.1 (K), U5.3 (CA17)
unnamed: D528.1 (K), D560.1 (K), D592.1 (K), D624.1 (K), D656.1 (K), D688.1 (K), D720.1 (K), D752.1 (K), D784.1 (K), D816.1 (K), D848.1 (K), D880.1 (K), D912.1 (K), D944.1 (K), D976.1 (K), D1008.1 (K), U5.5 (CA19)
unnamed: D529.2 (A), D530.2 (A), D531.2 (A), D532.2 (A), D533.2 (A), D534.2 (A), D535.2 (A), D536.2 (A), D537.2 (A), D538.2 (A), D539.2 (A), D540.2 (A), D541.2 (A), D542.2 (A), D543.2 (A), D544.2 (A), D561.1 (K), D593.1 (K), D625.1 (K), D657.1 (K), D689.1 (K), D721.1 (K), D753.1 (K), D785.1 (K), D817.1 (K), D849.1 (K), D881.1 (K), D913.1 (K), D945.1 (K), D977.1 (K), D1009.1 (K), U6.12 (CA1)
unnamed: D543.1 (K), D575.1 (K), D607.1 (K), D639.1 (K), D671.1 (K), D703.1 (K), D735.1 (K), D767.1 (K), D799.1 (K), D831.1 (K), D863.1 (K), D895.1 (K), D927.1 (K), D959.1 (K), D991.1 (K), D1009.2 (A), D1010.2 (A), D1011.2 (A), D1012.2 (A), D1013.2 (A), D1014.2 (A), D1015.2 (A), D1016.2 (A), D1017.2 (A), D1018.2 (A), D1019.2 (A), D1020.2 (A), D1021.2 (A), D1022.2 (A), D1023.2 (A), D1024.2 (A), U6.4 (CA18)
unnamed: D529.1 (K), D561.2 (A), D562.2 (A), D563.2 (A), D564.2 (A), D565.2 (A), D566.2 (A), D567.2 (A), D568.2 (A), D569.2 (A), D570.2 (A), D571.2 (A), D572.2 (A), D573.2 (A), D574.2 (A), D575.2 (A), D576.2 (A), D594.1 (K), D626.1 (K), D658.1 (K), D690.1 (K), D722.1 (K), D754.1 (K), D786.1 (K), D818.1 (K), D850.1 (K), D882.1 (K), D914.1 (K), D946.1 (K), D978.1 (K), D1010.1 (K), U6.13 (CA2)
unnamed: D530.1 (K), D562.1 (K), D593.2 (A), D594.2 (A), D595.2 (A), D596.2 (A), D597.2 (A), D598.2 (A), D599.2 (A), D600.2 (A), D601.2 (A), D602.2 (A), D603.2 (A), D604.2 (A), D605.2 (A), D606.2 (A), D607.2 (A), D608.2 (A), D627.1 (K), D659.1 (K), D691.1 (K), D723.1 (K), D755.1 (K), D787.1 (K), D819.1 (K), D851.1 (K), D883.1 (K), D915.1 (K), D947.1 (K), D979.1 (K), D1011.1 (K), U6.14 (CA3)
unnamed: D531.1 (K), D563.1 (K), D595.1 (K), D625.2 (A), D626.2 (A), D627.2 (A), D628.2 (A), D629.2 (A), D630.2 (A), D631.2 (A), D632.2 (A), D633.2 (A), D634.2 (A), D635.2 (A), D636.2 (A), D637.2 (A), D638.2 (A), D639.2 (A), D640.2 (A), D660.1 (K), D692.1 (K), D724.1 (K), D756.1 (K), D788.1 (K), D820.1 (K), D852.1 (K), D884.1 (K), D916.1 (K), D948.1 (K), D980.1 (K), D1012.1 (K), U6.15 (CA4)
unnamed: D532.1 (K), D564.1 (K), D596.1 (K), D628.1 (K), D657.2 (A), D658.2 (A), D659.2 (A), D660.2 (A), D661.2 (A), D662.2 (A), D663.2 (A), D664.2 (A), D665.2 (A), D666.2 (A), D667.2 (A), D668.2 (A), D669.2 (A), D670.2 (A), D671.2 (A), D672.2 (A), D693.1 (K), D725.1 (K), D757.1 (K), D789.1 (K), D821.1 (K), D853.1 (K), D885.1 (K), D917.1 (K), D949.1 (K), D981.1 (K), D1013.1 (K), U6.17 (CA5)
unnamed: D533.1 (K), D565.1 (K), D597.1 (K), D629.1 (K), D661.1 (K), D689.2 (A), D690.2 (A), D691.2 (A), D692.2 (A), D693.2 (A), D694.2 (A), D695.2 (A), D696.2 (A), D697.2 (A), D698.2 (A), D699.2 (A), D700.2 (A), D701.2 (A), D702.2 (A), D703.2 (A), D704.2 (A), D726.1 (K), D758.1 (K), D790.1 (K), D822.1 (K), D854.1 (K), D886.1 (K), D918.1 (K), D950.1 (K), D982.1 (K), D1014.1 (K), U6.18 (CA6)
unnamed: D534.1 (K), D566.1 (K), D598.1 (K), D630.1 (K), D662.1 (K), D694.1 (K), D721.2 (A), D722.2 (A), D723.2 (A), D724.2 (A), D725.2 (A), D726.2 (A), D727.2 (A), D728.2 (A), D729.2 (A), D730.2 (A), D731.2 (A), D732.2 (A), D733.2 (A), D734.2 (A), D735.2 (A), D736.2 (A), D759.1 (K), D791.1 (K), D823.1 (K), D855.1 (K), D887.1 (K), D919.1 (K), D951.1 (K), D983.1 (K), D1015.1 (K), U6.19 (CA7)
unnamed: D535.1 (K), D567.1 (K), D599.1 (K), D631.1 (K), D663.1 (K), D695.1 (K), D727.1 (K), D753.2 (A), D754.2 (A), D755.2 (A), D756.2 (A), D757.2 (A), D758.2 (A), D759.2 (A), D760.2 (A), D761.2 (A), D762.2 (A), D763.2 (A), D764.2 (A), D765.2 (A), D766.2 (A), D767.2 (A), D768.2 (A), D792.1 (K), D824.1 (K), D856.1 (K), D888.1 (K), D920.1 (K), D952.1 (K), D984.1 (K), D1016.1 (K), U6.20 (CA8)
unnamed: D536.1 (K), D568.1 (K), D600.1 (K), D632.1 (K), D664.1 (K), D696.1 (K), D728.1 (K), D760.1 (K), D785.2 (A), D786.2 (A), D787.2 (A), D788.2 (A), D789.2 (A), D790.2 (A), D791.2 (A), D792.2 (A), D793.2 (A), D794.2 (A), D795.2 (A), D796.2 (A), D797.2 (A), D798.2 (A), D799.2 (A), D800.2 (A), D825.1 (K), D857.1 (K), D889.1 (K), D921.1 (K), D953.1 (K), D985.1 (K), D1017.1 (K), U6.23 (CA10)
unnamed: D537.1 (K), D569.1 (K), D601.1 (K), D633.1 (K), D665.1 (K), D697.1 (K), D729.1 (K), D761.1 (K), D793.1 (K), D817.2 (A), D818.2 (A), D819.2 (A), D820.2 (A), D821.2 (A), D822.2 (A), D823.2 (A), D824.2 (A), D825.2 (A), D826.2 (A), D827.2 (A), D828.2 (A), D829.2 (A), D830.2 (A), D831.2 (A), D832.2 (A), D858.1 (K), D890.1 (K), D922.1 (K), D954.1 (K), D986.1 (K), D1018.1 (K), U6.25 (CA12)
unnamed: D538.1 (K), D570.1 (K), D602.1 (K), D634.1 (K), D666.1 (K), D698.1 (K), D730.1 (K), D762.1 (K), D794.1 (K), D826.1 (K), D849.2 (A), D850.2 (A), D851.2 (A), D852.2 (A), D853.2 (A), D854.2 (A), D855.2 (A), D856.2 (A), D857.2 (A), D858.2 (A), D859.2 (A), D860.2 (A), D861.2 (A), D862.2 (A), D863.2 (A), D864.2 (A), D891.1 (K), D923.1 (K), D955.1 (K), D987.1 (K), D1019.1 (K), U6.26 (CA13)
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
